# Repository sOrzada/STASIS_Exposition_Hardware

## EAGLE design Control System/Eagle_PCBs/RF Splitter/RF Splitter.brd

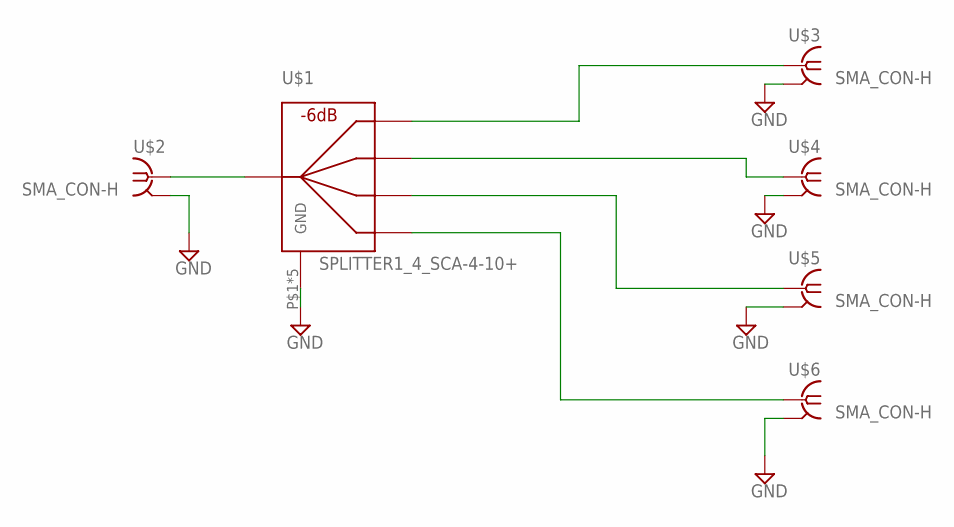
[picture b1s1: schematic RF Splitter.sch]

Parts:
U$1: SPLITTER1_4_SCA-4-10+; SCA-4-10+
U$2, U$3, U$4, U$5, U$6: SMA_CON-H; BU-SMA-H

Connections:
GND: U$1.P$1 (GND), U$1.P$2 (GND), U$1.P$4 (GND), U$1.P$5 (GND), U$1.P$8 (GND), U$2.2 (GND), U$2.3 (GND), U$2.4 (GND), U$2.5 (GND), U$3.2 (GND), U$3.3 (GND), U$3.4 (GND), U$3.5 (GND), U$4.2 (GND), U$4.3 (GND), U$4.4 (GND), U$4.5 (GND), U$5.2 (GND), U$5.3 (GND), U$5.4 (GND), U$5.5 (GND), U$6.2 (GND), U$6.3 (GND), U$6.4 (GND), U$6.5 (GND)
unnamed: U$1.P$3, U$2.1
unnamed: U$1.P$6, U$3.1
unnamed: U$1.P$7, U$4.1
unnamed: U$1.P$9, U$5.1
unnamed: U$1.P$10, U$6.1

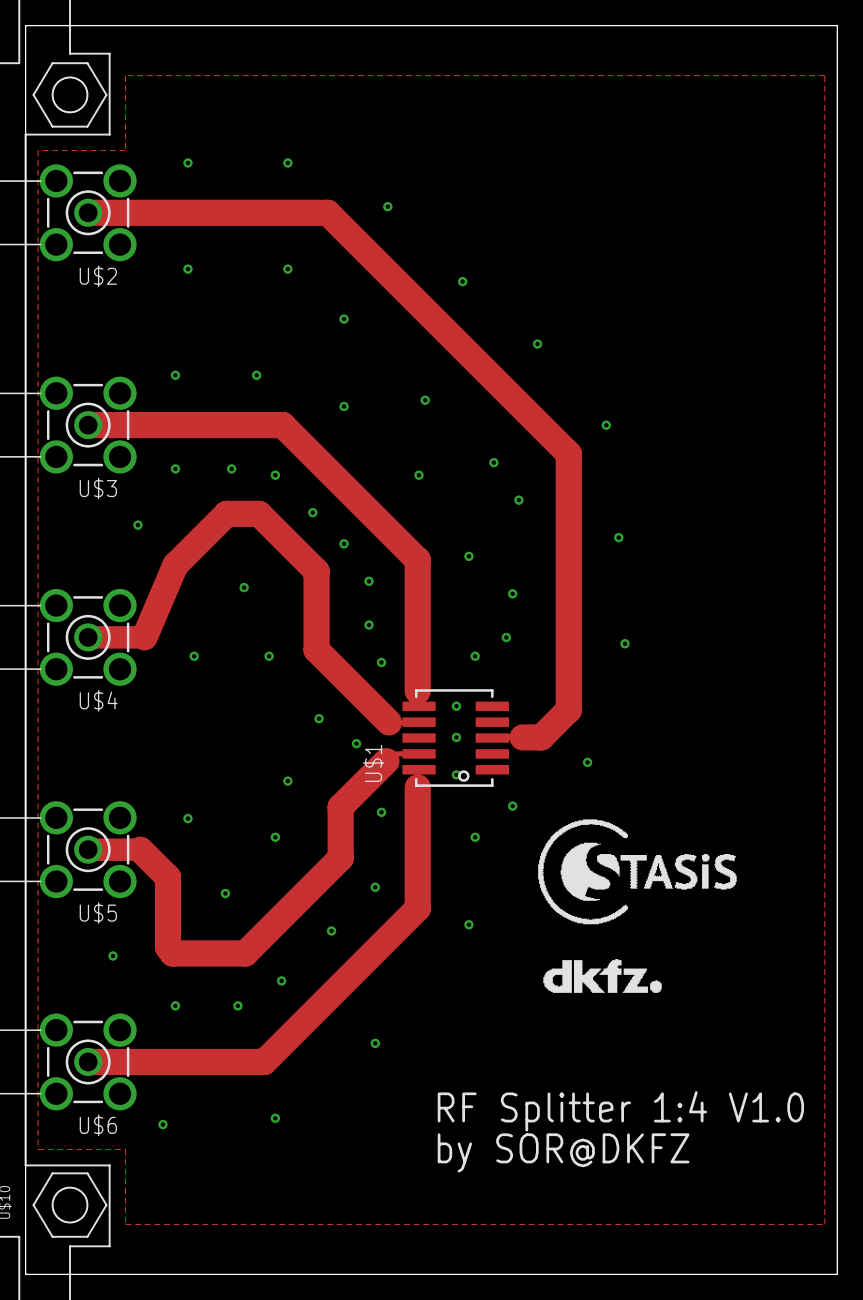
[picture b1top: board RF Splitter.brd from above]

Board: 2 copper layers, 65.0 x 100.0 mm, 9 parts (0 on the bottom side), 6 nets.

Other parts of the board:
U$8: LOGO_STASIS
U$9: LOGO_DKFZ
U$10: FPH

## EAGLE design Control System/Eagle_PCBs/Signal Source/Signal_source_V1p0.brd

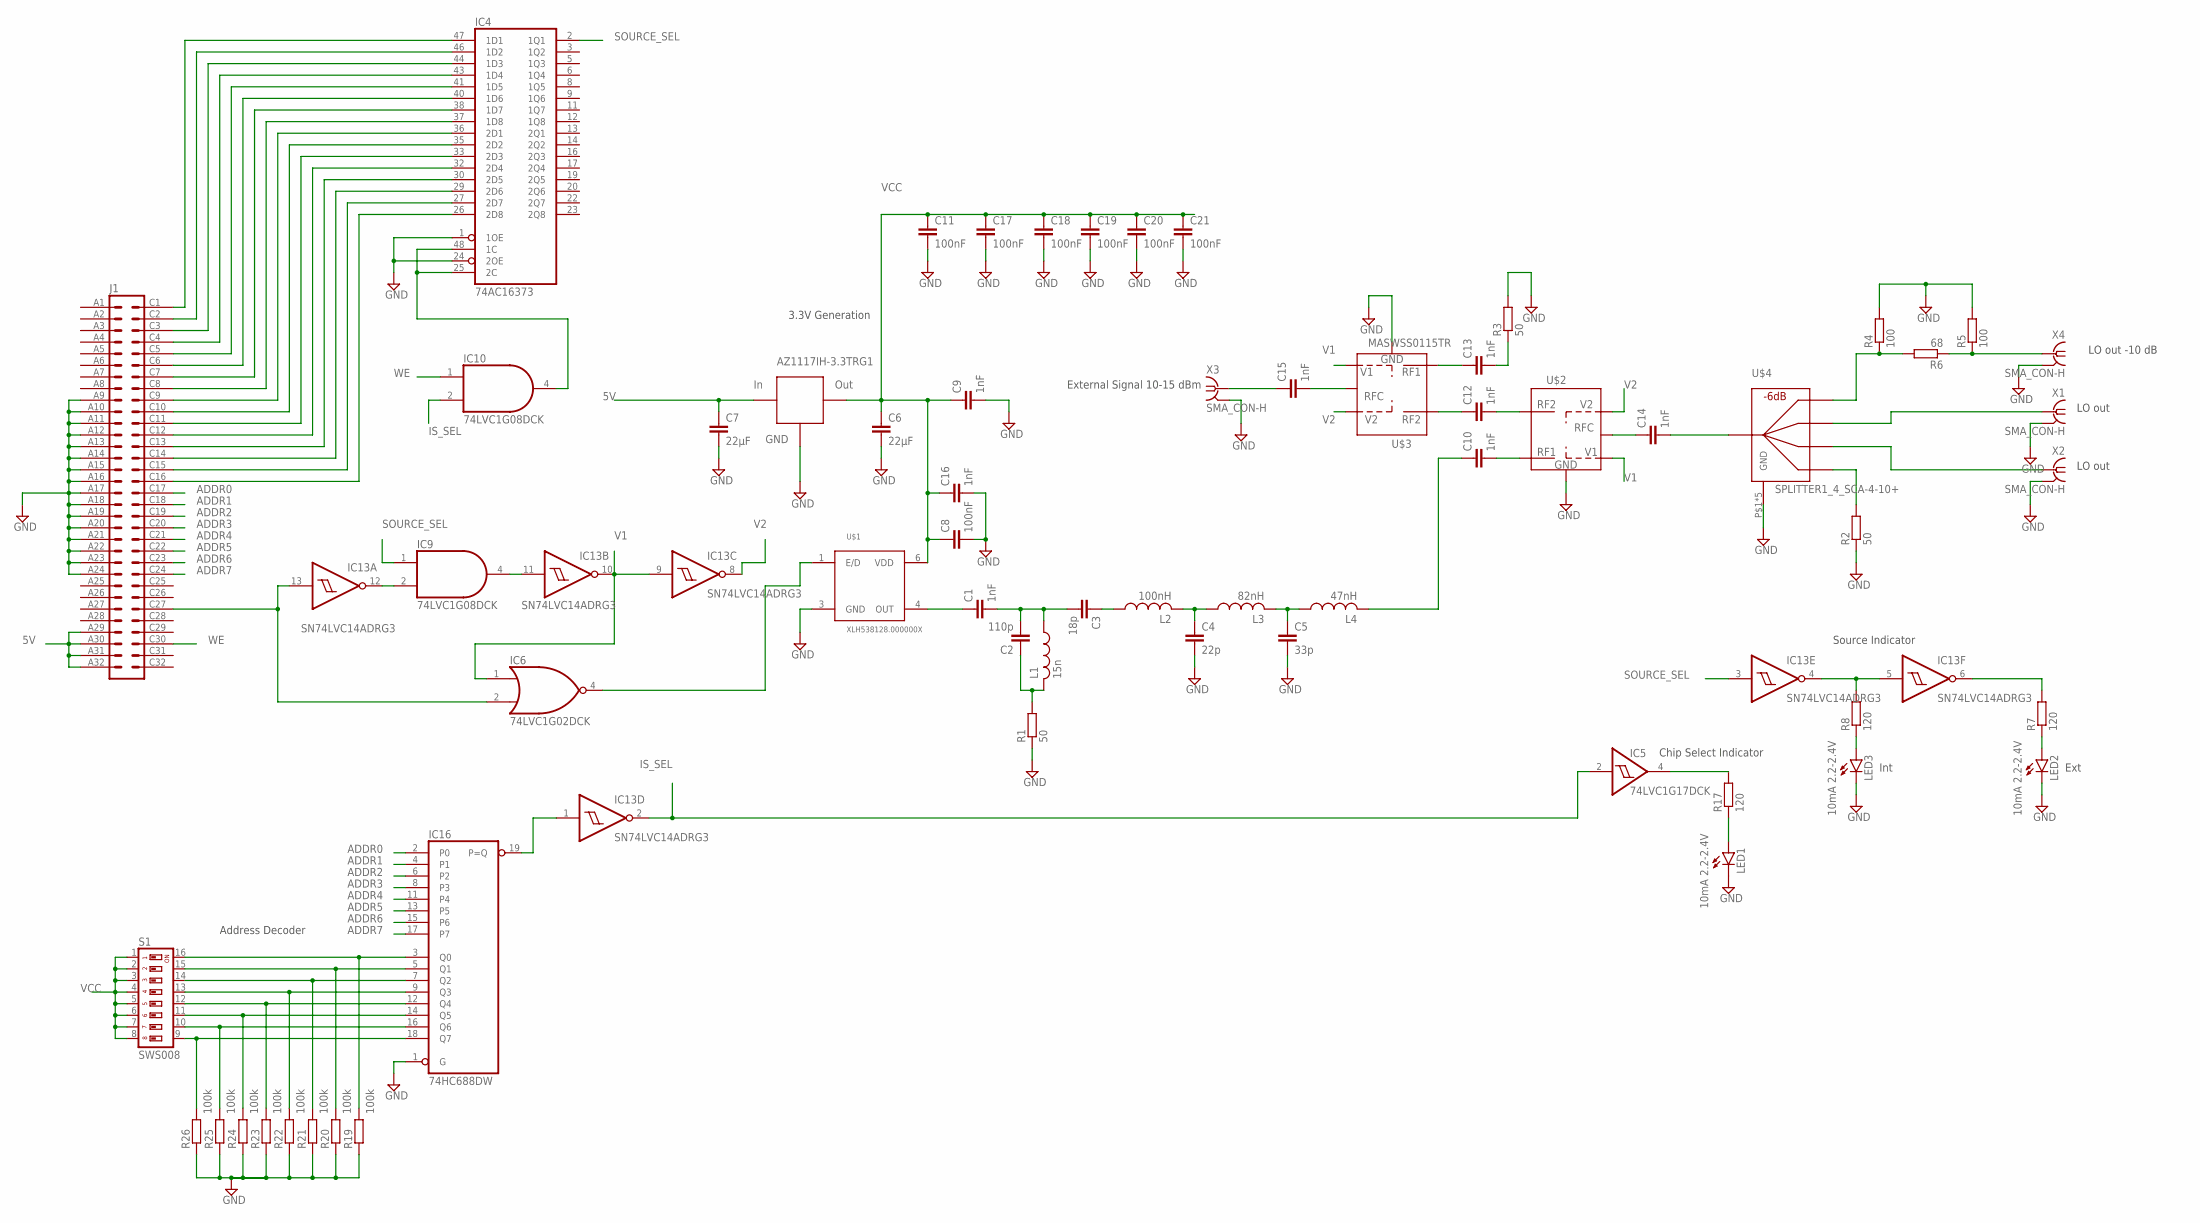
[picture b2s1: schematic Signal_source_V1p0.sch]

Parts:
C1, C9, C10, C12, C13, C14, C15, C16: 1nF; C0805
C2: 110p; C0805
C3: 18p; C0805
C4: 22p; C0805
C5: 33p; C0805
C6, C7: 22µF; C1206
C8, C11, C17, C18, C19, C20, C21: 100nF; C1206
IC4: 74AC16373; SSOP48DL
IC5: 74LVC1G17DCK; SC70-5
IC6: 74LVC1G02DCK; SC70-5
IC9, IC10: 74LVC1G08DCK; SC70-5
IC13: SN74LVC14ADRG3; SO14
IC16: 74HC688DW; SO20W
J1: VG64P
L1: 15n; L3225M
L2: 100nH; L3225M
L3: 82nH; L3225M
L4: 47nH; L3225M
LED1, LED2, LED3: 10mA 2.2-2.4V; LED3MM
R1, R2, R3: 50; R0805
R4, R5: 100; R0805
R6: 68; R0805
R7, R8, R17: 120; R0603
R19, R20, R21, R22, R23, R24, R25, R26: 100k; R0603
S1: SWS008; SMS-008
U$1: XLH538128.000000X; 5.0X3.2_XO
U$2, U$3: MASWSS0115TR; SC70-6
U$4: SPLITTER1_4_SCA-4-10+; SCA-4-10+
U$9: AZ1117IH-3.3TRG1; SOT223
X1, X2, X3, X4: SMA_CON-H; BU-SMA-H

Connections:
5V: C7.1, J1.A29, J1.A30, J1.A31, J1.A32, U$9.3 (IN)
ADDR0: IC16.2 (P0), J1.C17
ADDR1: IC16.4 (P1), J1.C18
ADDR2: IC16.6 (P2), J1.C19
ADDR3: IC16.8 (P3), J1.C20
ADDR4: IC16.11 (P4), J1.C21
ADDR5: IC16.13 (P5), J1.C22
ADDR6: IC16.15 (P6), J1.C23
ADDR7: IC16.17 (P7), J1.C24
CLK_128: C1.1, U$1.4 (OUT)
GND: C4.2, C5.2, C6.2, C7.2, C8.2, C9.2, C11.2, C16.2, C17.2, C18.2, C19.2, C20.2, C21.2, IC4.1 (1OE), IC4.4 (GND), IC4.10 (GND), IC4.15 (GND), IC4.21 (GND), IC4.24 (2OE), IC4.28 (GND), IC4.34 (GND), IC4.39 (GND), IC4.45 (GND), IC5.3 (GND), IC6.3 (GND), IC9.3 (GND), IC10.3 (GND), IC13.7 (GND), IC16.1 (G), IC16.10 (GND), J1.A9, J1.A10, J1.A11, J1.A12, J1.A13, J1.A14, J1.A15, J1.A16, J1.A17, J1.A18, J1.A19, J1.A20, J1.A21, J1.A22, J1.A23, J1.A24, LED1.K (C), LED2.K (C), LED3.K (C), R1.1, R2.1, R3.2, R4.2, R5.2, R19.1, R20.1, R21.1, R22.1, R23.1, R24.1, R25.1, R26.1, U$1.3 (GND), U$2.2 (GND), U$3.2 (GND), U$4.P$1 (GND), U$4.P$2 (GND), U$4.P$4 (GND), U$4.P$5 (GND), U$4.P$8 (GND), U$9.1 (GND), X1.2 (GND), X1.3 (GND), X1.4 (GND), X1.5 (GND), X2.2 (GND), X2.3 (GND), X2.4 (GND), X2.5 (GND), X3.2 (GND), X3.3 (GND), X3.4 (GND), X3.5 (GND), X4.2 (GND), X4.3 (GND), X4.4 (GND), X4.5 (GND)
IS_SEL: IC5.2 (I), IC10.2 (I1), IC13.2 (O)
unnamed: IC4.47 (1D1), J1.C1
unnamed: C1.2, C2.2, C3.2, L1.1
unnamed: C2.1, L1.2, R1.2
unnamed: C3.1, L2.1
unnamed: C4.1, L2.2, L3.1
unnamed: C5.1, L3.2, L4.1
unnamed: IC4.46 (1D2), J1.C2
unnamed: IC4.44 (1D3), J1.C3
unnamed: C10.1, L4.2
unnamed: IC4.43 (1D4), J1.C4
unnamed: IC4.41 (1D5), J1.C5
unnamed: IC4.40 (1D6), J1.C6
unnamed: C10.2, U$2.1 (RF1)
unnamed: IC4.38 (1D7), J1.C7
unnamed: IC4.37 (1D8), J1.C8
unnamed: C12.1, U$3.3 (RF2)
unnamed: C12.2, U$2.3 (RF2)
unnamed: C13.1, U$3.1 (RF1)
unnamed: C13.2, R3.1
unnamed: C15.2, U$3.5 (RFC)
unnamed: C14.1, U$2.5 (RFC)
unnamed: C14.2, U$4.P$3
unnamed: C15.1, X3.1
unnamed: IC9.2 (I1), IC13.12 (O)
unnamed: IC4.36 (2D1), J1.C9
unnamed: IC4.35 (2D2), J1.C10
unnamed: IC4.33 (2D3), J1.C11
unnamed: IC4.32 (2D4), J1.C12
unnamed: IC4.30 (2D5), J1.C13
unnamed: IC4.29 (2D6), J1.C14
unnamed: IC4.27 (2D7), J1.C15
unnamed: IC4.26 (2D8), J1.C16
unnamed: IC6.4 (O), U$1.1 (E/D)
unnamed: IC6.2 (I1), IC13.13 (I), J1.C27
unnamed: IC9.4 (O), IC13.11 (I)
unnamed: IC4.25 (2C), IC4.48 (1C), IC10.4 (O)
unnamed: U$4.P$7, X1.1
unnamed: U$4.P$9, X2.1
unnamed: R2.2, U$4.P$10
unnamed: IC16.3 (Q0), R19.2, S1.16
unnamed: R4.1, R6.2, U$4.P$6
unnamed: R5.1, R6.1, X4.1
unnamed: IC13.4 (O), IC13.5 (I), R8.2
unnamed: IC13.6 (O), R7.2
unnamed: LED3.A, R8.1
unnamed: LED2.A, R7.1
unnamed: IC16.5 (Q1), R20.2, S1.15
unnamed: IC16.7 (Q2), R21.2, S1.14
unnamed: IC16.9 (Q3), R22.2, S1.13
unnamed: IC16.12 (Q4), R23.2, S1.12
unnamed: IC16.14 (Q5), R24.2, S1.11
unnamed: IC16.16 (Q6), R25.2, S1.10
unnamed: IC16.18 (Q7), R26.2, S1.9
unnamed: IC13.1 (I), IC16.19 (P=Q)
unnamed: LED1.A, R17.1
unnamed: IC5.4 (O), R17.2
SOURCE_SEL: IC4.2 (1Q1), IC9.1 (I0), IC13.3 (I)
V1: IC6.1 (I0), IC13.9 (I), IC13.10 (O), U$2.6 (V1), U$3.6 (V1)
V2: IC13.8 (O), U$2.4 (V2), U$3.4 (V2)
VCC: C6.1, C8.1, C9.1, C11.1, C16.1, C17.1, C18.1, C19.1, C20.1, C21.1, IC4.7 (VCC), IC4.18 (VCC), IC4.31 (VCC), IC4.42 (VCC), IC5.5 (VCC), IC6.5 (VCC), IC9.5 (VCC), IC10.5 (VCC), IC13.14 (VCC), IC16.20 (VCC), S1.1, S1.2, S1.3, S1.4, S1.5, S1.6, S1.7, S1.8, U$1.6 (VDD), U$9.2 (OUT), U$9.4 (OUT)
WE: IC10.1 (I0), J1.C30

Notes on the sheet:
External Signal 10-15 dBm
LO out
Address Decoder
Chip Select Indicator
LO out -10 dB
Source Indicator
Int
Ext
3.3V Generation

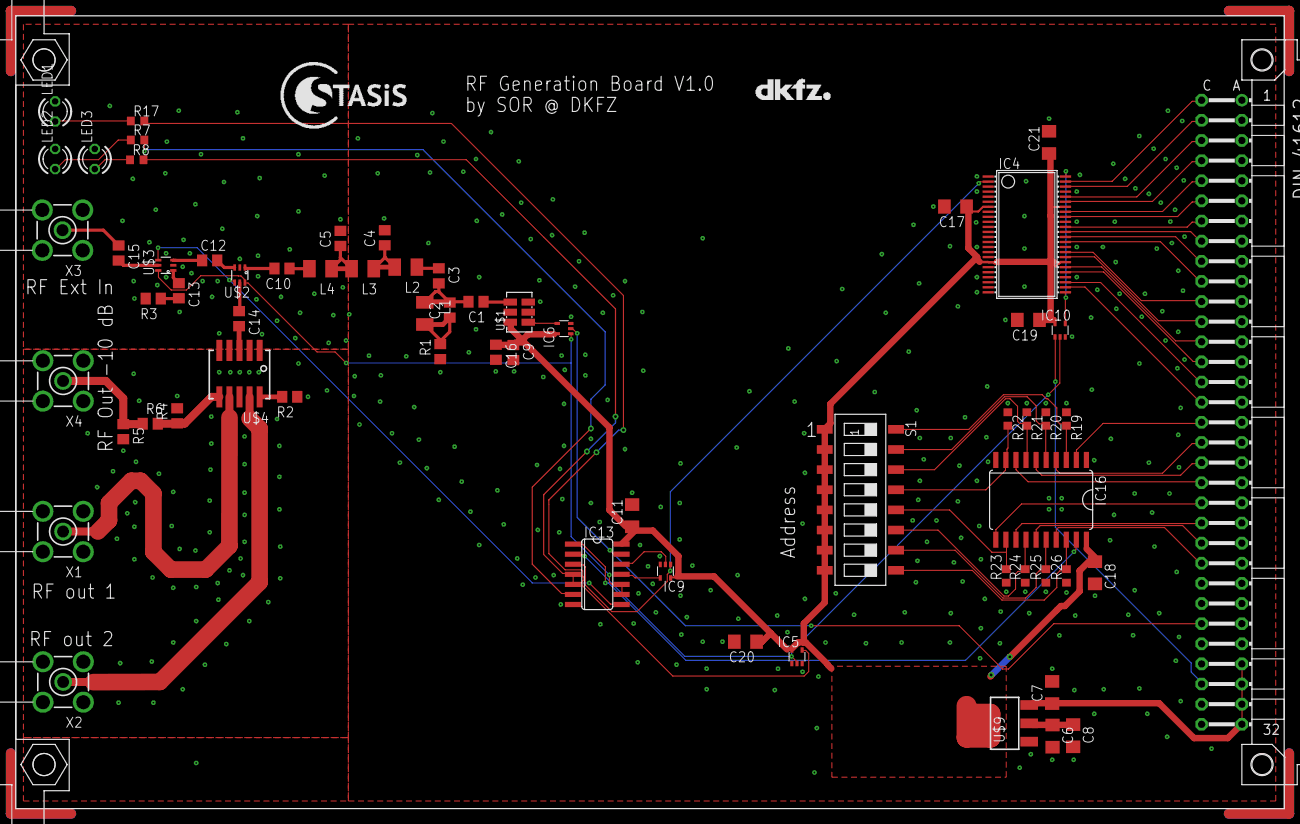
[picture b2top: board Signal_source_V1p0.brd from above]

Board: 2 copper layers, 160.0 x 100.0 mm, 65 parts (0 on the bottom side), 73 nets.

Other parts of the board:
U$5: LOGO_STASIS
U$6: LOGO_DKFZ

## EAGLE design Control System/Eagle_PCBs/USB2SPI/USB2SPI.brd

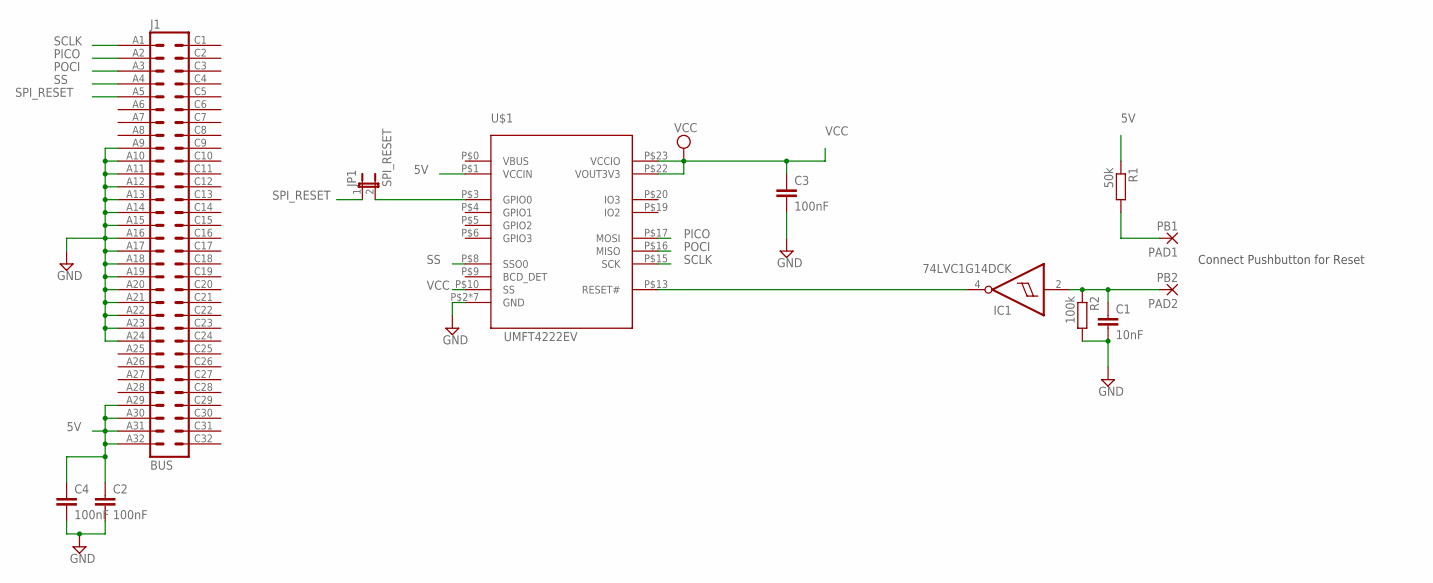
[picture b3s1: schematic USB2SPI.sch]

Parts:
C1: 10nF; C0603
C2, C3, C4: 100nF; C0603
IC1: 74LVC1G14DCK; SC70-5
J1: BUS; VG64P
JP1: SPI_RESET; JP1
PAD1: PB1; SMD2,54-5,08
PAD2: PB2; SMD2,54-5,08
R1: 50k; R0603
R2: 100k; R0603
U$1: UMFT4222EV

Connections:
5V: C2.1, C4.1, J1.A29, J1.A30, J1.A31, J1.A32, R1.1, U$1.P$1 (VCCIN)
GND: C1.2, C2.2, C3.2, C4.2, IC1.3 (GND), J1.A9, J1.A10, J1.A11, J1.A12, J1.A13, J1.A14, J1.A15, J1.A16, J1.A17, J1.A18, J1.A19, J1.A20, J1.A21, J1.A22, J1.A23, J1.A24, R2.2, U$1.P$2 (GND), U$1.P$7 (GND), U$1.P$11 (GND), U$1.P$12 (GND), U$1.P$14 (GND), U$1.P$18 (GND), U$1.P$21 (GND)
unnamed: JP1.2, U$1.P$3 (GPIO0)
unnamed: IC1.4 (O), U$1.P$13 (RESET#)
unnamed: C1.1, IC1.2 (I), PAD2.1, R2.1
unnamed: PAD1.1, R1.2
PICO: J1.A2, U$1.P$17 (MOSI)
POCI: J1.A3, U$1.P$16 (MISO)
SCLK: J1.A1, U$1.P$15 (SCK)
SPI_RESET: J1.A5, JP1.1
SS: J1.A4, U$1.P$8 (SSO0)
VCC: C3.1, IC1.5 (VCC), U$1.P$10 (SS), U$1.P$22 (VOUT3V3), U$1.P$23 (VCCIO)

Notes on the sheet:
Connect Pushbutton for Reset

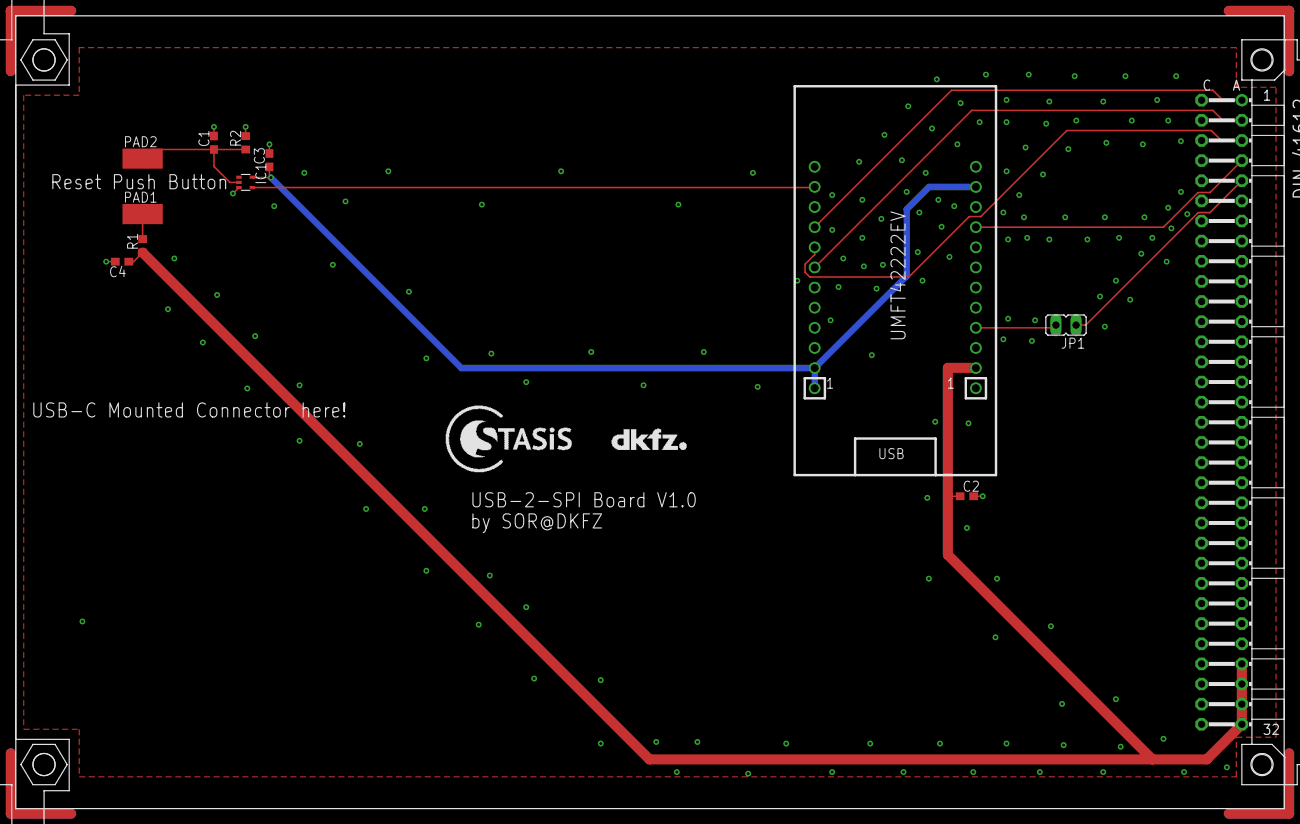
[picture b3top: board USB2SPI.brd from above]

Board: 2 copper layers, 160.0 x 100.0 mm, 14 parts (0 on the bottom side), 12 nets.

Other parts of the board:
U$2: LOGO_STASIS
U$3: LOGO_DKFZ

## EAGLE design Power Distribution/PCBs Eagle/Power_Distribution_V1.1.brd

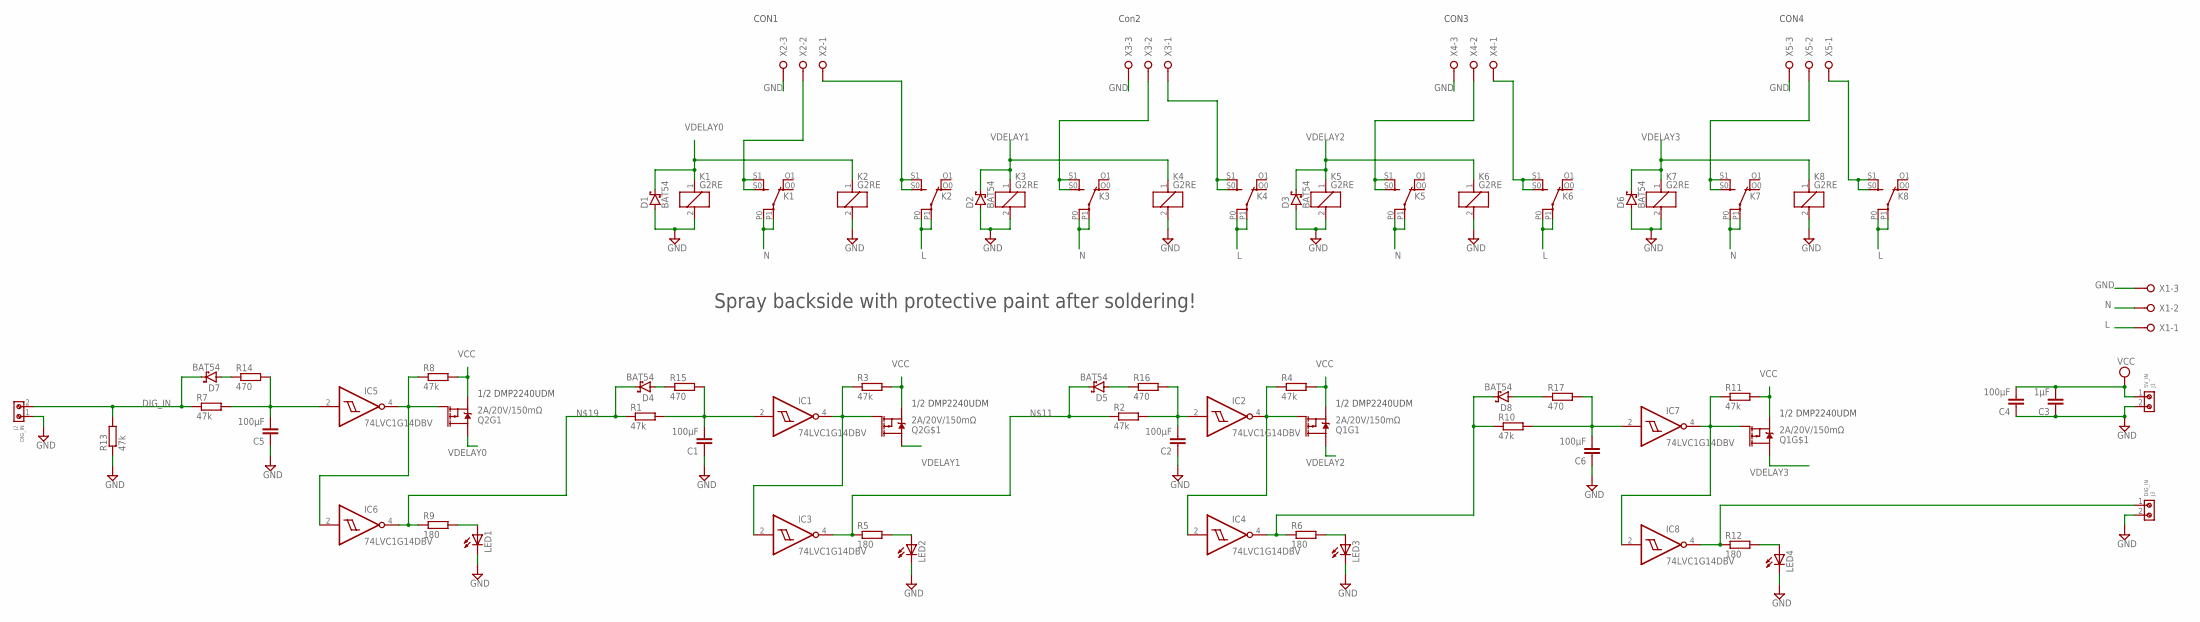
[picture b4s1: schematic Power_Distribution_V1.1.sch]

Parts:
C1, C2, C4, C5, C6: 100µF; C1210
C3: 1µF; C1210
D1, D2, D3, D4, D5, D6, D7, D8: BAT54; SOT23
IC1, IC2, IC3, IC4, IC5, IC6, IC7, IC8: 74LVC1G14DBV; SOT23-5
J1: 5V_IN; 691210910002
J2, J3: DIG_IN; 691210910002
K1, K2, K3, K4, K5, K6, K7, K8: G2RE
LED1, LED2, LED3, LED4: LED3MM
Q1, Q2: 2A/20V/150mΩ; SOT26
R1, R2, R3, R4, R7, R8, R10, R11, R13: 47k; R0805
R5, R6, R9, R12: 180; R0805
R14, R15, R16, R17: 470; R0805
X1, X2, X3, X4, X5: W237-3E

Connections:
DIG_IN: D7.3 (C), J2.2, R7.1, R13.2
GND: C1.1, C2.1, C3.1, C4.1, C5.1, C6.1, D1.1 (A), D2.1 (A), D3.1 (A), D6.1 (A), IC1.3 (GND), IC2.3 (GND), IC3.3 (GND), IC4.3 (GND), IC5.3 (GND), IC6.3 (GND), IC7.3 (GND), IC8.3 (GND), J1.2, J2.1, J3.2, K1.2, K2.2, K3.2, K4.2, K5.2, K6.2, K7.2, K8.2, LED1.K (C), LED2.K (C), LED3.K (C), LED4.K (C), R13.1, X1.3, X2.3, X3.3, X4.3, X5.3
L: K2.P0, K2.P1, K4.P0, K4.P1, K6.P0, K6.P1, K8.P0, K8.P1, X1.1
N: K1.P0, K1.P1, K3.P0, K3.P1, K5.P0, K5.P1, K7.P0, K7.P1, X1.2
unnamed: K1.S0 (S), K1.S1 (S), X2.2
unnamed: K2.S0 (S), K2.S1 (S), X2.1
unnamed: K3.S0 (S), K3.S1 (S), X3.2
unnamed: K4.S0 (S), K4.S1 (S), X3.1
unnamed: K5.S0 (S), K5.S1 (S), X4.2
unnamed: K6.S0 (S), K6.S1 (S), X4.1
unnamed: IC1.4 (O), IC3.2 (I), Q2.G2 (G), R3.1
unnamed: IC2.4 (O), IC4.2 (I), Q1.G1 (G), R4.1
unnamed: C2.2, IC2.2 (I), R2.2, R16.2
unnamed: C1.2, IC1.2 (I), R1.2, R15.2
unnamed: D5.3 (C), IC3.4 (O), R2.1, R5.1
unnamed: LED2.A, R5.2
unnamed: D8.3 (C), IC4.4 (O), R6.1, R10.1
unnamed: LED3.A, R6.2
unnamed: K7.S0 (S), K7.S1 (S), X5.2
unnamed: K8.S0 (S), K8.S1 (S), X5.1
unnamed: IC5.4 (O), IC6.2 (I), Q2.G1 (G), R8.1
unnamed: C5.2, IC5.2 (I), R7.2, R14.2
unnamed: D4.3 (C), IC6.4 (O), R1.1, R9.1
unnamed: LED1.A, R9.2
unnamed: IC7.4 (O), IC8.2 (I), Q1.G2 (G), R11.1
unnamed: C6.2, IC7.2 (I), R10.2, R17.2
unnamed: IC8.4 (O), J3.1, R12.1
unnamed: LED4.A, R12.2
unnamed: D7.1 (A), R14.1
unnamed: D4.1 (A), R15.1
unnamed: D5.1 (A), R16.1
unnamed: D8.1 (A), R17.1
VCC: C3.2, C4.2, IC1.5 (VCC), IC2.5 (VCC), IC3.5 (VCC), IC4.5 (VCC), IC5.5 (VCC), IC6.5 (VCC), IC7.5 (VCC), IC8.5 (VCC), J1.1, Q1.S1 (S), Q1.S2 (S), Q2.S1 (S), Q2.S2 (S), R3.2, R4.2, R8.2, R11.2
VDELAY0: D1.3 (C), K1.1, K2.1, Q2.D1 (D)
VDELAY1: D2.3 (C), K3.1, K4.1, Q2.D2 (D)
VDELAY2: D3.3 (C), K5.1, K6.1, Q1.D1 (D)
VDELAY3: D6.3 (C), K7.1, K8.1, Q1.D2 (D)

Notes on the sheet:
CON1
Con2
CON3
1/2 DMP2240UDM
CON4
Spray backside with protective paint after soldering!

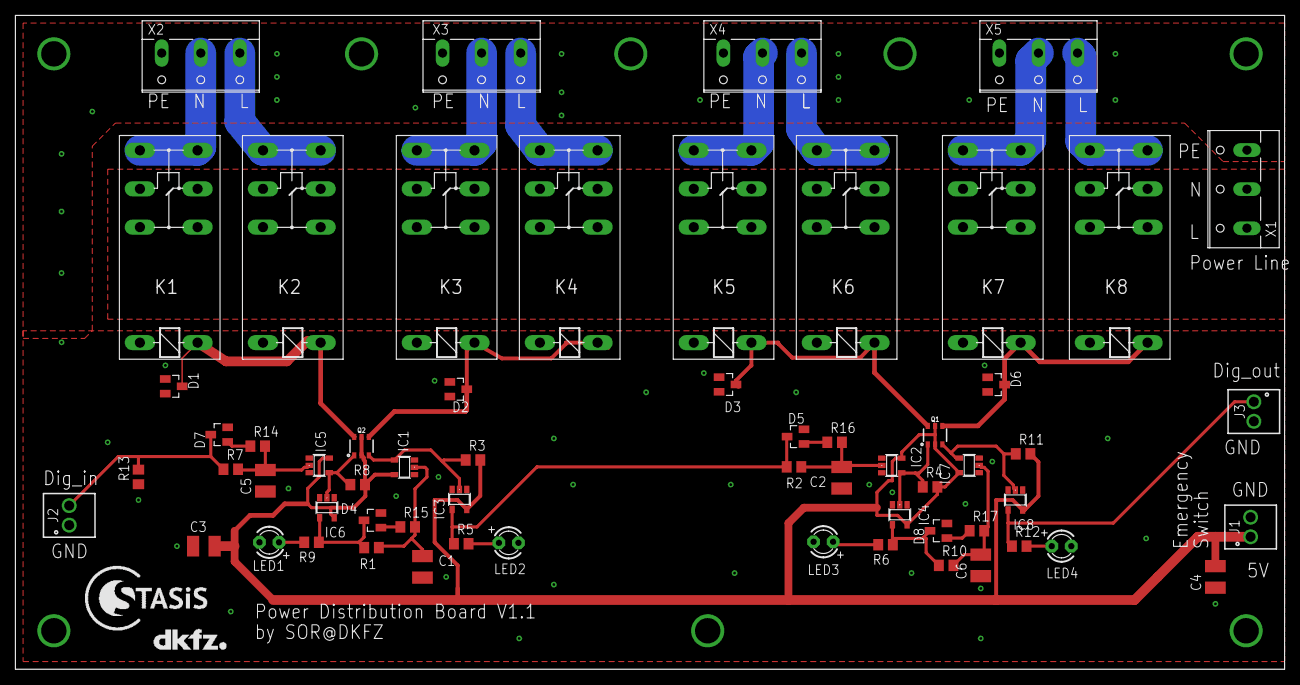
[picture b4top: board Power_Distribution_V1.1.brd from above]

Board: 2 copper layers, 165.0 x 85.0 mm, 63 parts (0 on the bottom side), 37 nets.

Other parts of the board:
U$1: LOGO_STASIS
U$2: LOGO_DKFZ

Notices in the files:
parts and their libraries:
Wurth_Connectors_WR-TBL Rising Cage Clam: Copyright: Würth Elektronik
SparkFun-DiscreteSemi: Licensing: Creative Commons ShareAlike 4.0 International - https://creativecommons.org/licenses/by-sa/4.0
